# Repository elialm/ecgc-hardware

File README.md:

# ecgc-hardware

This repo contains all relevant documentation of the cartridge hardware.

The `legacy` directory contains legacy documentation.
This is just a collection of documents I made *waaaay* back when I was
just starting on the project.
It is included here just as an archive so I don't plan on updating anything.

The `CartGen3ProtoBoard` directory contains the schematics for the
first working prototype mentioned at [my website](https://efacdev.nl/posts/ecgc/20220601).
The photograph below is this prototype.

[gen3prototype-photo](https://user-images.githubusercontent.com/43206514/217519505-81669f43-df62-44b2-97f7-6338e39c4504.png)

The `CartGen4` directory contains the schematics for the
next prototype.
I've included some renders of it below.

[gen4-render-front](/CartGen4/img/front.png)  
[gen4-render-back](/CartGen4/img/back.png)

# Development tools

The tools used to make the schematics is [KiCad](https://www.kicad.org/).
It can be used to open the `*.kicad_pro` file to open the schematic
project.

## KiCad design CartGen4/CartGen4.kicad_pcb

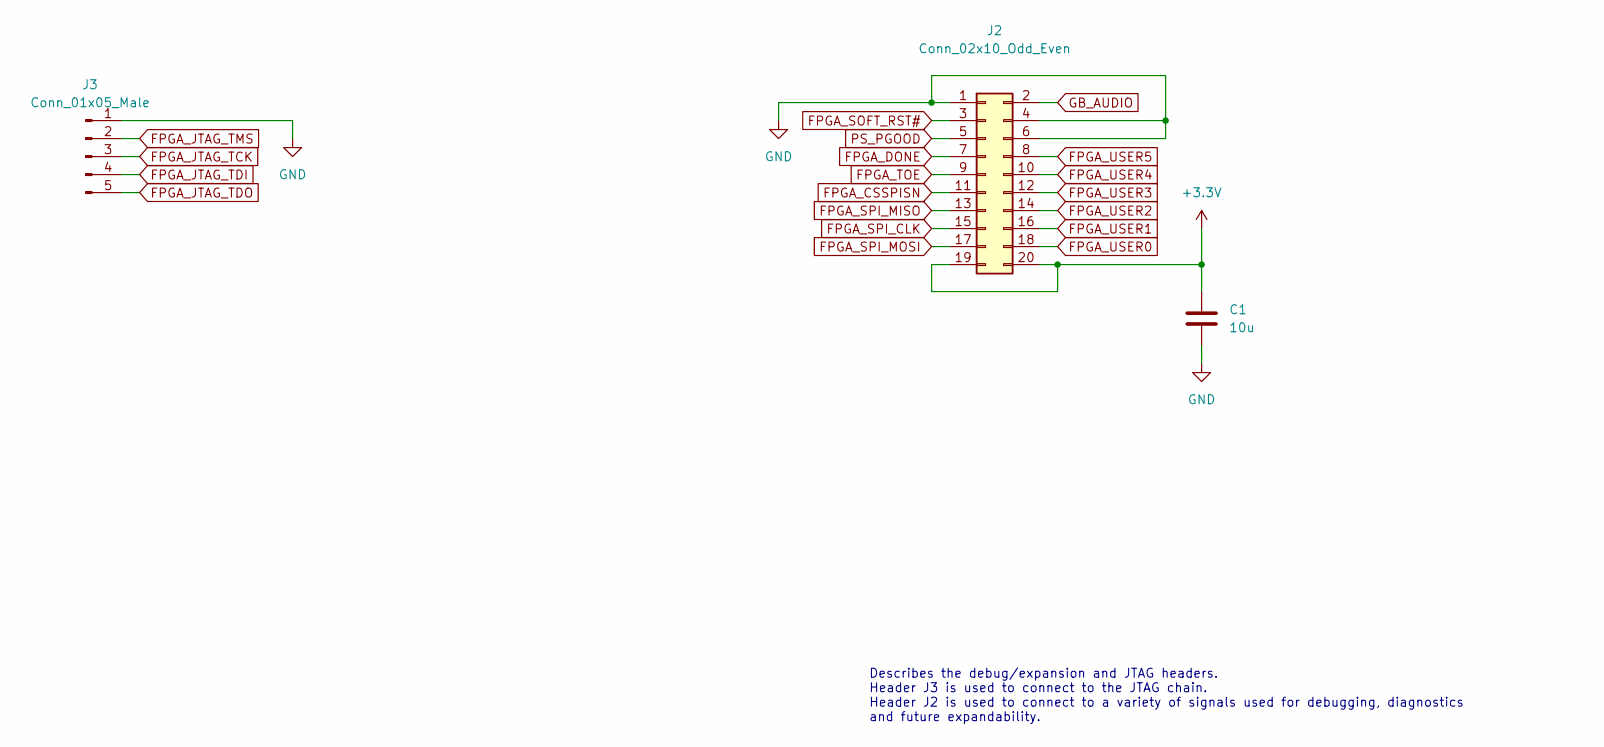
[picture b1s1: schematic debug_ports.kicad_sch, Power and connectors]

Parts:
C1: 10u; C_0603_1608Metric_Pad1.08x0.95mm_HandSolder; Tolerance 20%; Voltage 10V
J2: Conn_02x10_Odd_Even; Conn_02x10
J3: Conn_01x05_Male; PinHeader_1x05_P1.27mm_Vertical

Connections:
FPGA_CSSPISN: J2.11; also elsewhere on the board
FPGA_DONE: J2.7; also elsewhere on the board
FPGA_JTAG_TCK: J3.3; also elsewhere on the board
FPGA_JTAG_TDI: J3.4; also elsewhere on the board
FPGA_JTAG_TDO: J3.5; also elsewhere on the board
FPGA_JTAG_TMS: J3.2; also elsewhere on the board
FPGA_SOFT_RST#: J2.3; also elsewhere on the board
FPGA_SPI_CLK: J2.15; also elsewhere on the board
FPGA_SPI_MISO: J2.13; also elsewhere on the board
FPGA_SPI_MOSI: J2.17; also elsewhere on the board
FPGA_TOE: J2.9; also elsewhere on the board
FPGA_USER0: J2.18; also elsewhere on the board
FPGA_USER1: J2.16; also elsewhere on the board
FPGA_USER2: J2.14; also elsewhere on the board
FPGA_USER3: J2.12; also elsewhere on the board
FPGA_USER4: J2.10; also elsewhere on the board
FPGA_USER5: J2.8; also elsewhere on the board
GB_AUDIO: J2.2; also elsewhere on the board
GND: C1.2, J2.1, J2.4, J2.6, J3.1; also elsewhere on the board
PS_PGOOD: J2.5; also elsewhere on the board

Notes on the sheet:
Describes the debug/expansion and JTAG headers. Header J3 is used to connect to the JTAG chain. Header J2 is used to connect to a variety of signals used for debugging, diagnostics and future expandability.

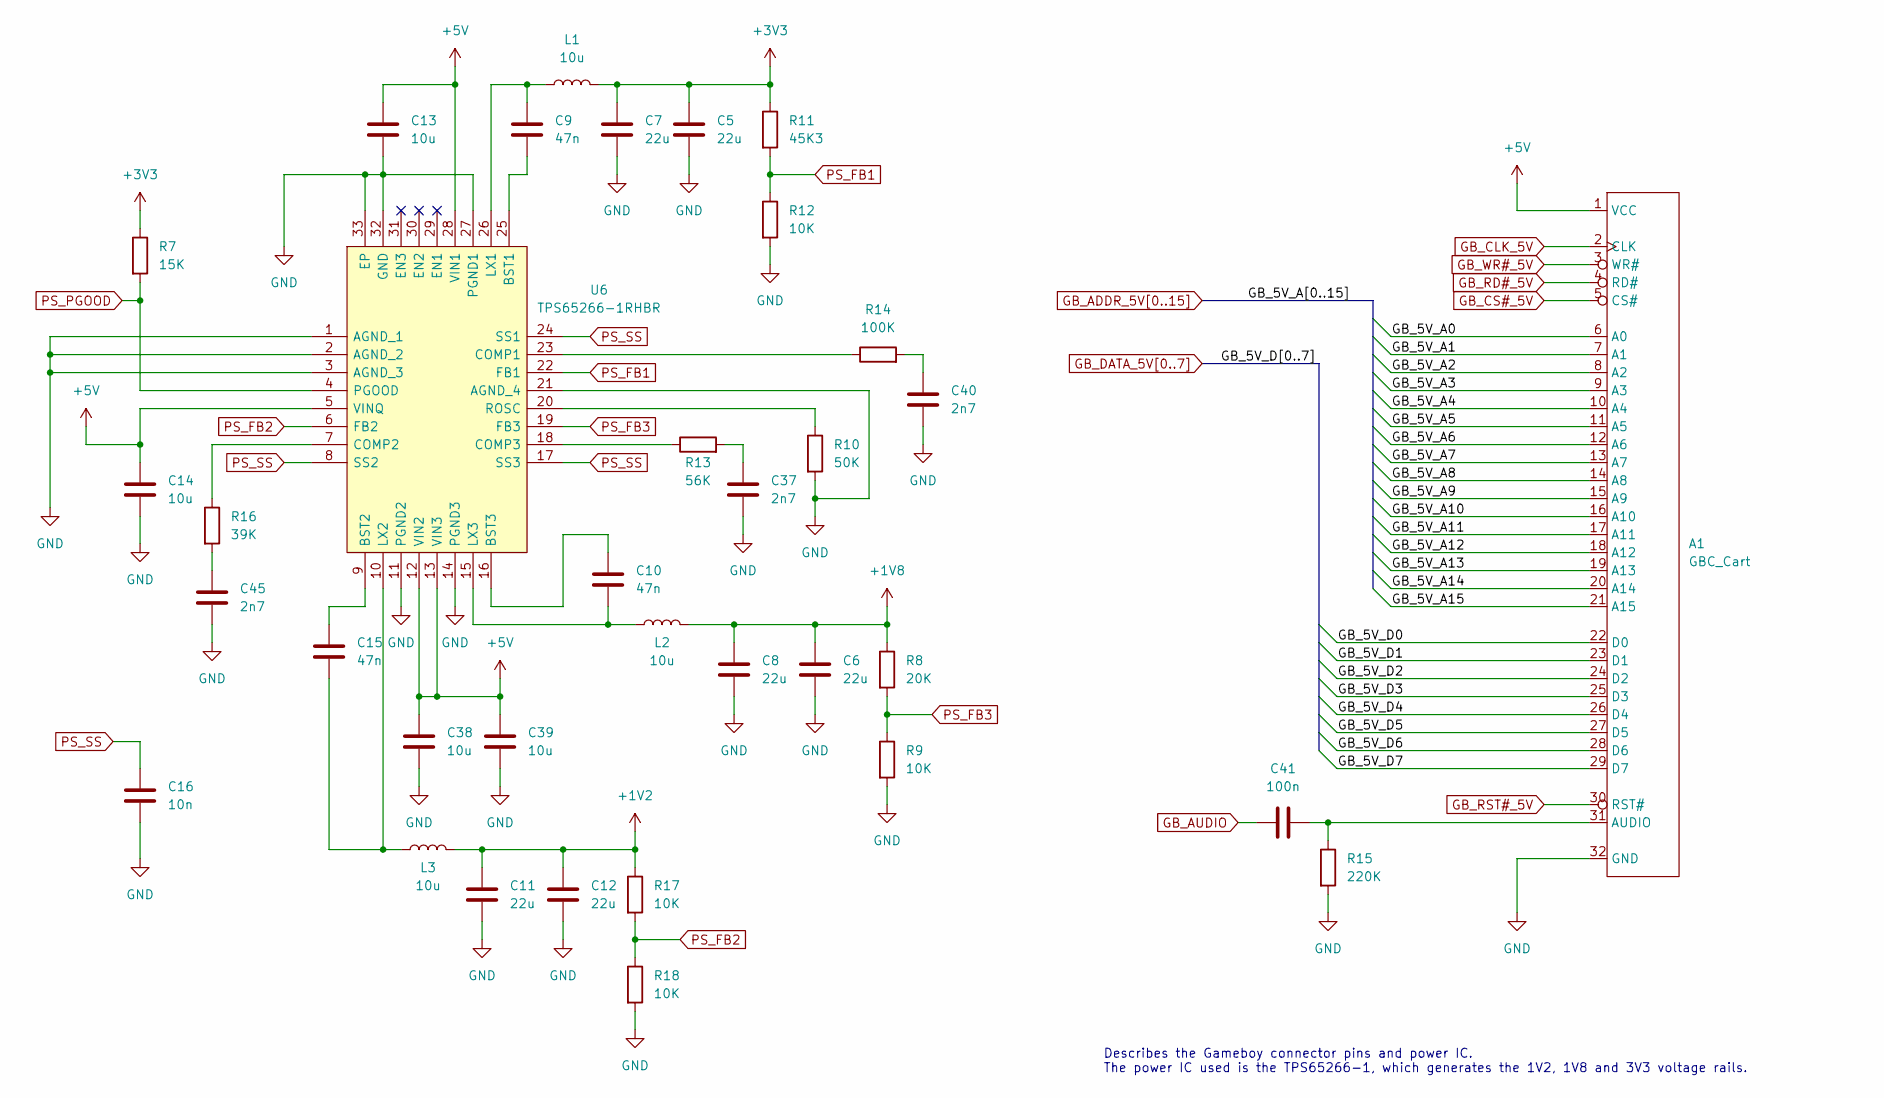
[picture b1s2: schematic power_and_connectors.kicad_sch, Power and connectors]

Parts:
A1: GBC_Cart
C5, C6, C7, C8, C11, C12: 22u; C_0603_1608Metric_Pad1.08x0.95mm_HandSolder; Tolerance 20%; Voltage 3V3
C9, C10, C15: 47n; C_0402_1005Metric_Pad0.74x0.62mm_HandSolder; Voltage 10V; Tolerance 5%
C13, C14, C38, C39: 10u; C_0603_1608Metric_Pad1.08x0.95mm_HandSolder; Voltage 10V; Tolerance 20%
C16: 10n; C_0402_1005Metric_Pad0.74x0.62mm_HandSolder; Tolerance 20%; Voltage 3V3
C37, C40, C45: 2n7; C_0402_1005Metric_Pad0.74x0.62mm_HandSolder; Tolerance 5%; Voltage 3V3
C41: 100n; C_0603_1608Metric_Pad1.08x0.95mm_HandSolder
L1, L2, L3: 10u; L_1008_2520Metric; Tolerance 20%
R7: 15K; R_0402_1005Metric_Pad0.72x0.64mm_HandSolder; Tolerance 10%
R8: 20K; R_0402_1005Metric_Pad0.72x0.64mm_HandSolder; Tolerance 1%
R9, R12, R17, R18: 10K; R_0402_1005Metric_Pad0.72x0.64mm_HandSolder; Tolerance 1%
R10: 50K; R_0402_1005Metric_Pad0.72x0.64mm_HandSolder; Tolerance 1%
R11: 45K3; R_0402_1005Metric_Pad0.72x0.64mm_HandSolder; Tolerance 1%
R13: 56K; R_0402_1005Metric_Pad0.72x0.64mm_HandSolder; Tolerance 1%
R14: 100K; R_0402_1005Metric_Pad0.72x0.64mm_HandSolder; Tolerance 1%
R15: 220K; R_0402_1005Metric_Pad0.72x0.64mm_HandSolder; Tolerance 10%
R16: 39K; R_0402_1005Metric_Pad0.72x0.64mm_HandSolder; Tolerance 1%
U6: TPS65266-1RHBR; QFN50P500X500X100-33N-D

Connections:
+1V2: C11.1, C12.1, L3.2, R17.1; also elsewhere on the board
+1V8: C6.1, C8.1, L2.2, R8.1; also elsewhere on the board
+5V: A1.1 (VCC), C13.1, C14.1, C38.1, C39.1, U6.5 (VINQ), U6.12 (VIN2), U6.13 (VIN3), U6.28 (VIN1); also elsewhere on the board
GB_ADDR_5V0: A1.6 (A0); also elsewhere on the board
GB_ADDR_5V1: A1.7 (A1); also elsewhere on the board
GB_ADDR_5V2: A1.8 (A2); also elsewhere on the board
GB_ADDR_5V3: A1.9 (A3); also elsewhere on the board
GB_ADDR_5V4: A1.10 (A4); also elsewhere on the board
GB_ADDR_5V5: A1.11 (A5); also elsewhere on the board
GB_ADDR_5V6: A1.12 (A6); also elsewhere on the board
GB_ADDR_5V7: A1.13 (A7); also elsewhere on the board
GB_ADDR_5V8: A1.14 (A8); also elsewhere on the board
GB_ADDR_5V9: A1.15 (A9); also elsewhere on the board
GB_ADDR_5V10: A1.16 (A10); also elsewhere on the board
GB_ADDR_5V11: A1.17 (A11); also elsewhere on the board
GB_ADDR_5V12: A1.18 (A12); also elsewhere on the board
GB_ADDR_5V13: A1.19 (A13); also elsewhere on the board
GB_ADDR_5V14: A1.20 (A14); also elsewhere on the board
GB_ADDR_5V15: A1.21 (A15); also elsewhere on the board
GB_AUDIO: C41.1; also elsewhere on the board
GB_CLK_5V: A1.2 (CLK); also elsewhere on the board
GB_CS#_5V: A1.5 (CS#); also elsewhere on the board
GB_DATA_5V0: A1.22 (D0); also elsewhere on the board
GB_DATA_5V1: A1.23 (D1); also elsewhere on the board
GB_DATA_5V2: A1.24 (D2); also elsewhere on the board
GB_DATA_5V3: A1.25 (D3); also elsewhere on the board
GB_DATA_5V4: A1.26 (D4); also elsewhere on the board
GB_DATA_5V5: A1.27 (D5); also elsewhere on the board
GB_DATA_5V6: A1.28 (D6); also elsewhere on the board
GB_DATA_5V7: A1.29 (D7); also elsewhere on the board
GB_RD#_5V: A1.4 (RD#); also elsewhere on the board
GB_RST#_5V: A1.30 (RST#); also elsewhere on the board
GB_WR#_5V: A1.3 (WR#); also elsewhere on the board
GND: A1.32 (GND), C5.2, C6.2, C7.2, C8.2, C11.2, C12.2, C13.2, C14.2, C16.2, C37.2, C38.2, C39.2, C40.2, C45.2, R9.2, R10.2, R12.2, R15.2, R18.2, U6.1 (AGND_1), U6.2 (AGND_2), U6.3 (AGND_3), U6.11 (PGND2), U6.14 (PGND3), U6.21 (AGND_4), U6.27 (PGND1), U6.32 (GND), U6.33 (EP); also elsewhere on the board
unnamed: A1.31 (AUDIO), C41.2, R15.1
unnamed: C45.1, R16.2
unnamed: C15.1, U6.9 (BST2)
unnamed: C15.2, L3.1, U6.10 (LX2)
unnamed: C9.1, L1.1, U6.26 (LX1)
unnamed: C9.2, U6.25 (BST1)
unnamed: C10.1, U6.16 (BST3)
unnamed: C10.2, L2.1, U6.15 (LX3)
unnamed: C37.1, R13.2
unnamed: C40.1, R14.2
unnamed: R16.1, U6.7 (COMP2)
unnamed: R13.1, U6.18 (COMP3)
unnamed: R10.1, U6.20 (ROSC)
unnamed: R14.1, U6.23 (COMP1)
PS_FB1: R11.2, R12.1, U6.22 (FB1)
PS_FB2: R17.2, R18.1, U6.6 (FB2)
PS_FB3: R8.2, R9.1, U6.19 (FB3)
PS_PGOOD: R7.2, U6.4 (PGOOD); also elsewhere on the board
PS_SS: C16.1, U6.8 (SS2), U6.17 (SS3), U6.24 (SS1)

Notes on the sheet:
Describes the Gameboy connector pins and power IC. The power IC used is the TPS65266-1, which generates the 1V2, 1V8 and 3V3 voltage rails.

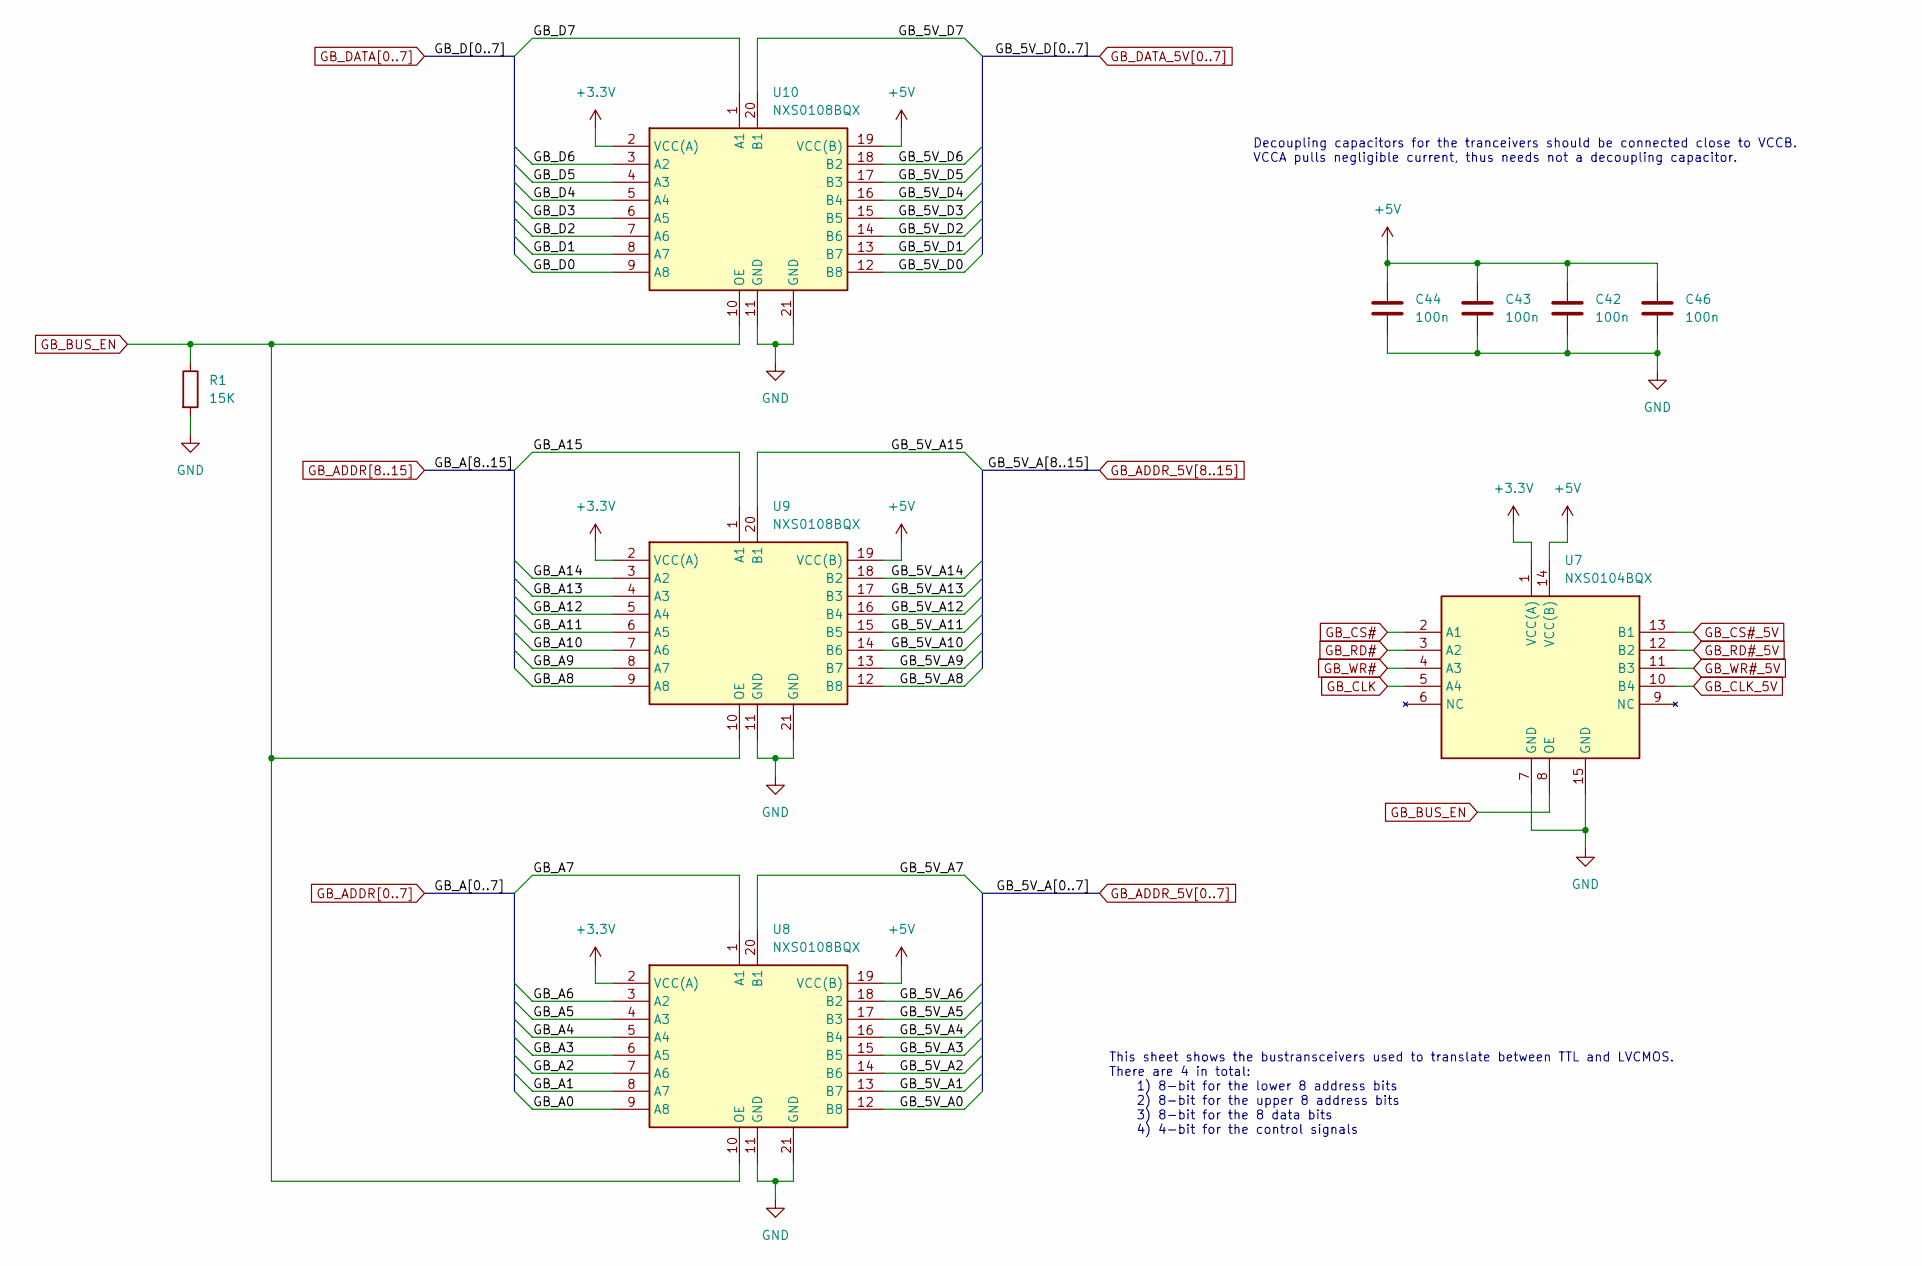
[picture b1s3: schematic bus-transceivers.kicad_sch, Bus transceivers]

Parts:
C42, C43, C44, C46: 100n; C_0402_1005Metric_Pad0.74x0.62mm_HandSolder; Tolerance 20%; Voltage 3V3
R1: 15K; R_0402_1005Metric_Pad0.72x0.64mm_HandSolder; Tolerance 10%
U7: NXS0104BQX
U8, U9, U10: NXS0108BQX

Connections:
+5V: C42.1, C43.1, C44.1, C46.1, U7.14 (VCC(B)), U8.19 (VCC(B)), U9.19 (VCC(B)), U10.19 (VCC(B)); also elsewhere on the board
GB_ADDR0: U8.9 (A8); also elsewhere on the board
GB_ADDR1: U8.8 (A7); also elsewhere on the board
GB_ADDR2: U8.7 (A6); also elsewhere on the board
GB_ADDR3: U8.6 (A5); also elsewhere on the board
GB_ADDR4: U8.5 (A4); also elsewhere on the board
GB_ADDR5: U8.4 (A3); also elsewhere on the board
GB_ADDR6: U8.3 (A2); also elsewhere on the board
GB_ADDR7: U8.1 (A1); also elsewhere on the board
GB_ADDR8: U9.9 (A8); also elsewhere on the board
GB_ADDR9: U9.8 (A7); also elsewhere on the board
GB_ADDR10: U9.7 (A6); also elsewhere on the board
GB_ADDR11: U9.6 (A5); also elsewhere on the board
GB_ADDR12: U9.5 (A4); also elsewhere on the board
GB_ADDR13: U9.4 (A3); also elsewhere on the board
GB_ADDR14: U9.3 (A2); also elsewhere on the board
GB_ADDR15: U9.1 (A1); also elsewhere on the board
GB_ADDR_5V0: U8.12 (B8); also elsewhere on the board
GB_ADDR_5V1: U8.13 (B7); also elsewhere on the board
GB_ADDR_5V2: U8.14 (B6); also elsewhere on the board
GB_ADDR_5V3: U8.15 (B5); also elsewhere on the board
GB_ADDR_5V4: U8.16 (B4); also elsewhere on the board
GB_ADDR_5V5: U8.17 (B3); also elsewhere on the board
GB_ADDR_5V6: U8.18 (B2); also elsewhere on the board
GB_ADDR_5V7: U8.20 (B1); also elsewhere on the board
GB_ADDR_5V8: U9.12 (B8); also elsewhere on the board
GB_ADDR_5V9: U9.13 (B7); also elsewhere on the board
GB_ADDR_5V10: U9.14 (B6); also elsewhere on the board
GB_ADDR_5V11: U9.15 (B5); also elsewhere on the board
GB_ADDR_5V12: U9.16 (B4); also elsewhere on the board
GB_ADDR_5V13: U9.17 (B3); also elsewhere on the board
GB_ADDR_5V14: U9.18 (B2); also elsewhere on the board
GB_ADDR_5V15: U9.20 (B1); also elsewhere on the board
GB_BUS_EN: R1.1, U7.8 (OE), U8.10 (OE), U9.10 (OE), U10.10 (OE); also elsewhere on the board
GB_CLK: U7.5 (A4); also elsewhere on the board
GB_CLK_5V: U7.10 (B4); also elsewhere on the board
GB_CS#: U7.2 (A1); also elsewhere on the board
GB_CS#_5V: U7.13 (B1); also elsewhere on the board
GB_DATA0: U10.9 (A8); also elsewhere on the board
GB_DATA1: U10.8 (A7); also elsewhere on the board
GB_DATA2: U10.7 (A6); also elsewhere on the board
GB_DATA3: U10.6 (A5); also elsewhere on the board
GB_DATA4: U10.5 (A4); also elsewhere on the board
GB_DATA5: U10.4 (A3); also elsewhere on the board
GB_DATA6: U10.3 (A2); also elsewhere on the board
GB_DATA7: U10.1 (A1); also elsewhere on the board
GB_DATA_5V0: U10.12 (B8); also elsewhere on the board
GB_DATA_5V1: U10.13 (B7); also elsewhere on the board
GB_DATA_5V2: U10.14 (B6); also elsewhere on the board
GB_DATA_5V3: U10.15 (B5); also elsewhere on the board
GB_DATA_5V4: U10.16 (B4); also elsewhere on the board
GB_DATA_5V5: U10.17 (B3); also elsewhere on the board
GB_DATA_5V6: U10.18 (B2); also elsewhere on the board
GB_DATA_5V7: U10.20 (B1); also elsewhere on the board
GB_RD#: U7.3 (A2); also elsewhere on the board
GB_RD#_5V: U7.12 (B2); also elsewhere on the board
GB_WR#: U7.4 (A3); also elsewhere on the board
GB_WR#_5V: U7.11 (B3); also elsewhere on the board
GND: C42.2, C43.2, C44.2, C46.2, R1.2, U7.7 (GND), U7.15 (GND), U8.11 (GND), U8.21 (GND), U9.11 (GND), U9.21 (GND), U10.11 (GND), U10.21 (GND); also elsewhere on the board

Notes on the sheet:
This sheet shows the bustransceivers used to translate between TTL and LVCMOS. There are 4 in total: 1) 8-bit for the lower 8 address bits 2) 8-bit for the upper 8 address bits 3) 8-bit for the 8 data bits 4) 4-bit for the control signals
Decoupling capacitors for the tranceivers should be connected close to VCCB. VCCA pulls negligible current, thus needs not a decoupling capacitor.

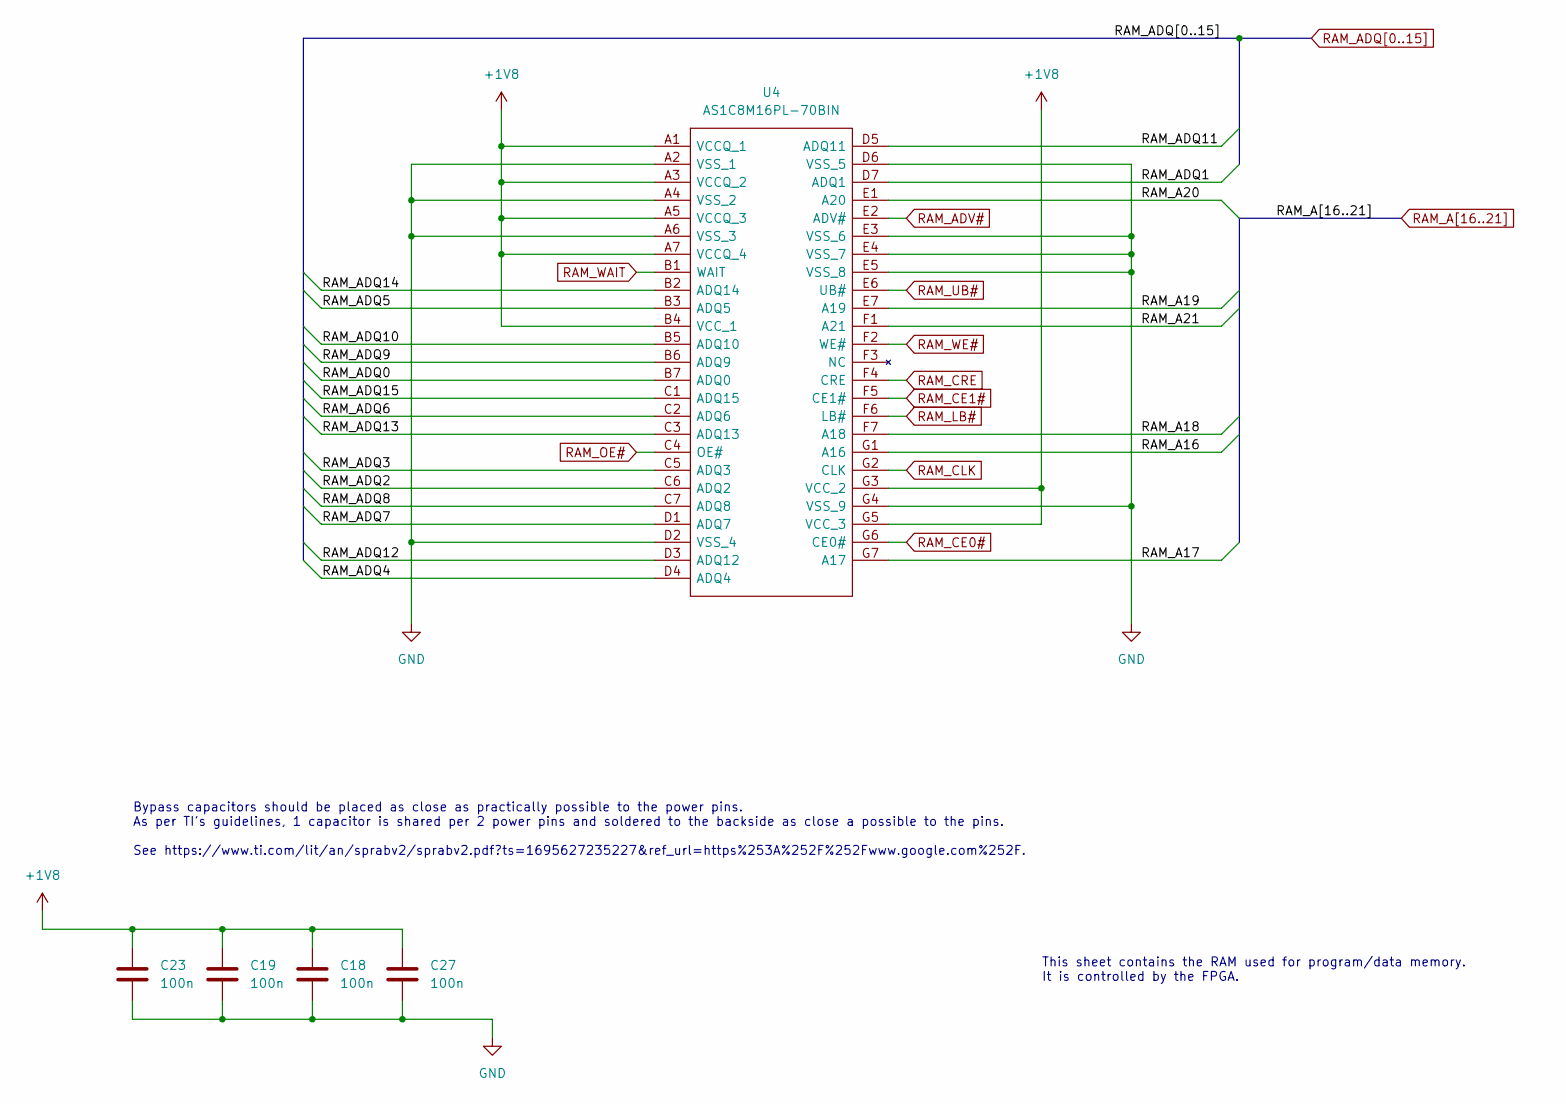
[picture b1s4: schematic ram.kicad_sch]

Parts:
C18, C19, C23, C27: 100n; C_0402_1005Metric_Pad0.74x0.62mm_HandSolder; Tolerance 20%; Voltage 3V3
U4: AS1C8M16PL-70BIN; BGA49C50P7X7_400X400X100

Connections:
+1V8: C18.1, C19.1, C23.1, C27.1, U4.A1 (VCCQ_1), U4.A3 (VCCQ_2), U4.A5 (VCCQ_3), U4.A7 (VCCQ_4), U4.B4 (VCC_1), U4.G3 (VCC_2), U4.G5 (VCC_3); also elsewhere on the board
GND: C18.2, C19.2, C23.2, C27.2, U4.A2 (VSS_1), U4.A4 (VSS_2), U4.A6 (VSS_3), U4.D2 (VSS_4), U4.D6 (VSS_5), U4.E3 (VSS_6), U4.E4 (VSS_7), U4.E5 (VSS_8), U4.G4 (VSS_9); also elsewhere on the board
RAM_A16: U4.G1 (A16); also elsewhere on the board
RAM_A17: U4.G7 (A17); also elsewhere on the board
RAM_A18: U4.F7 (A18); also elsewhere on the board
RAM_A19: U4.E7 (A19); also elsewhere on the board
RAM_A20: U4.E1 (A20); also elsewhere on the board
RAM_A21: U4.F1 (A21); also elsewhere on the board
RAM_ADQ0: U4.B7 (ADQ0); also elsewhere on the board
RAM_ADQ1: U4.D7 (ADQ1); also elsewhere on the board
RAM_ADQ2: U4.C6 (ADQ2); also elsewhere on the board
RAM_ADQ3: U4.C5 (ADQ3); also elsewhere on the board
RAM_ADQ4: U4.D4 (ADQ4); also elsewhere on the board
RAM_ADQ5: U4.B3 (ADQ5); also elsewhere on the board
RAM_ADQ6: U4.C2 (ADQ6); also elsewhere on the board
RAM_ADQ7: U4.D1 (ADQ7); also elsewhere on the board
RAM_ADQ8: U4.C7 (ADQ8); also elsewhere on the board
RAM_ADQ9: U4.B6 (ADQ9); also elsewhere on the board
RAM_ADQ10: U4.B5 (ADQ10); also elsewhere on the board
RAM_ADQ11: U4.D5 (ADQ11); also elsewhere on the board
RAM_ADQ12: U4.D3 (ADQ12); also elsewhere on the board
RAM_ADQ13: U4.C3 (ADQ13); also elsewhere on the board
RAM_ADQ14: U4.B2 (ADQ14); also elsewhere on the board
RAM_ADQ15: U4.C1 (ADQ15); also elsewhere on the board
RAM_ADV#: U4.E2 (ADV#); also elsewhere on the board
RAM_CE0#: U4.G6 (CE0#); also elsewhere on the board
RAM_CE1#: U4.F5 (CE1#); also elsewhere on the board
RAM_CLK: U4.G2 (CLK); also elsewhere on the board
RAM_CRE: U4.F4 (CRE); also elsewhere on the board
RAM_LB#: U4.F6 (LB#); also elsewhere on the board
RAM_OE#: U4.C4 (OE#); also elsewhere on the board
RAM_UB#: U4.E6 (UB#); also elsewhere on the board
RAM_WAIT: U4.B1 (WAIT); also elsewhere on the board
RAM_WE#: U4.F2 (WE#); also elsewhere on the board

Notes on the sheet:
This sheet contains the RAM used for program/data memory. It is controlled by the FPGA.
Bypass capacitors should be placed as close as practically possible to the power pins. As per TI's guidelines, 1 capacitor is shared per 2 power pins and soldered to the backside as close a possible to the pins. See https://www.ti.com/lit/an/sprabv2/sprabv2.pdf?ts=1695627235227&ref_url=https%253A%2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

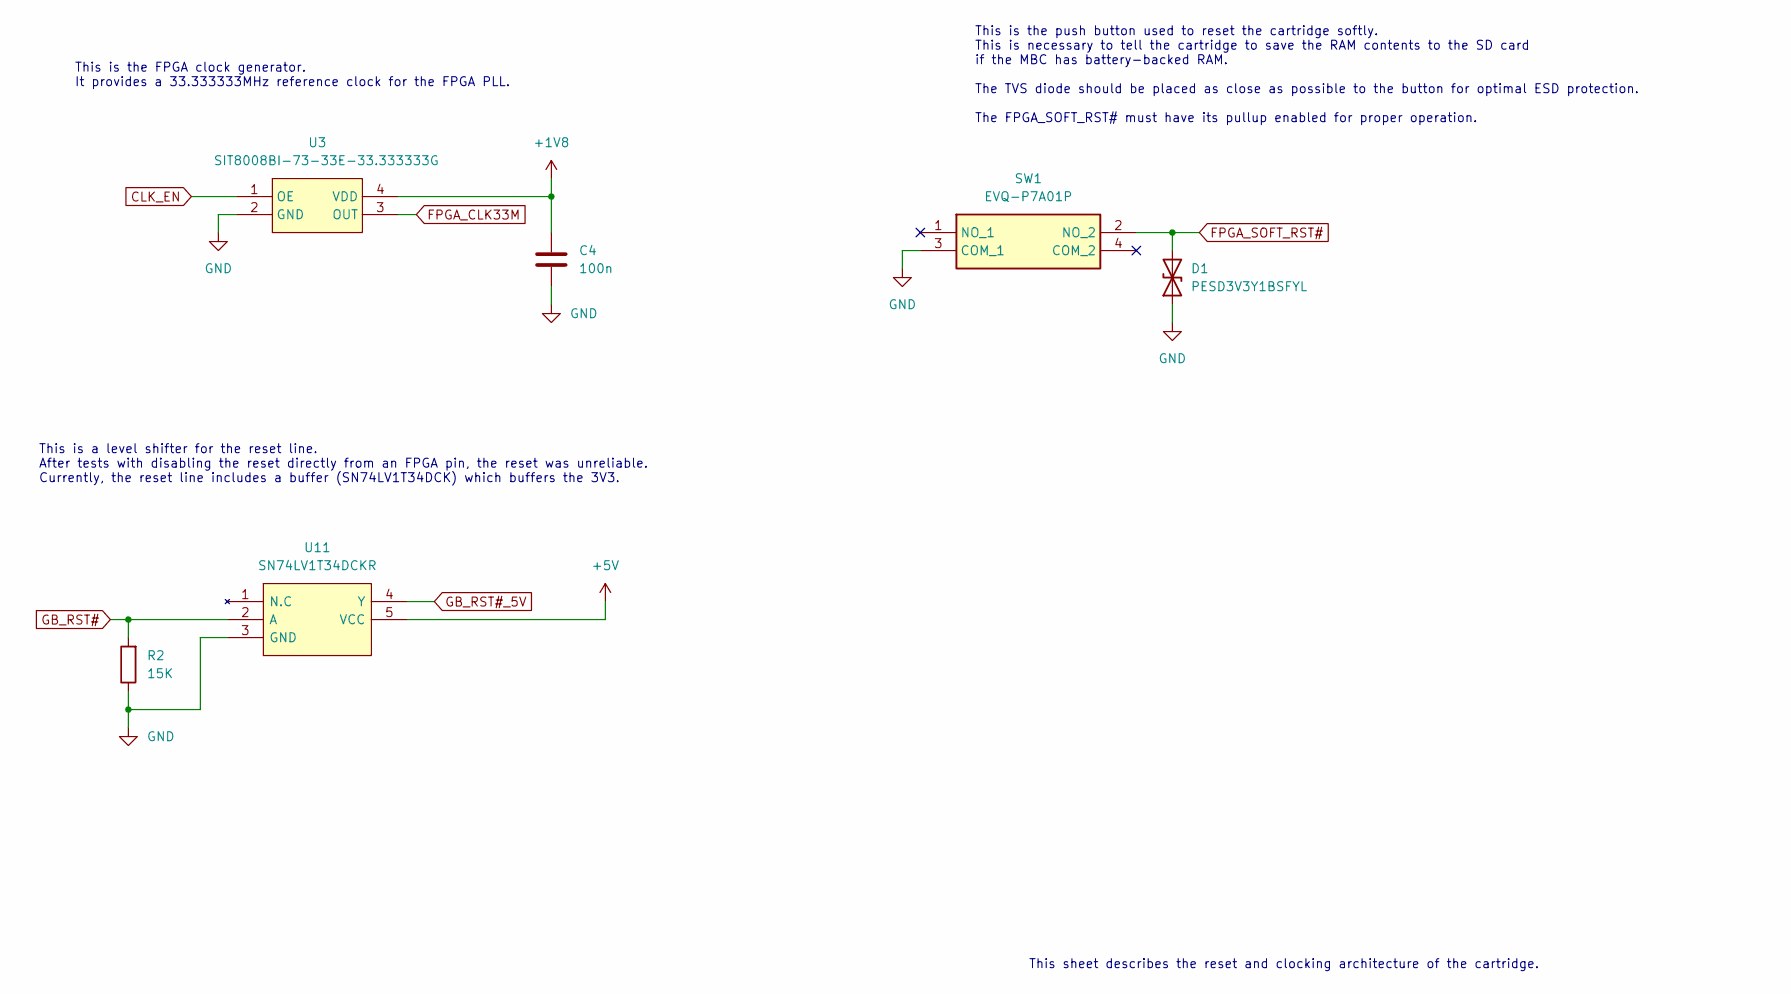
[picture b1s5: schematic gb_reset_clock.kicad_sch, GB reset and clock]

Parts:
C4: 100n; C_0402_1005Metric_Pad0.74x0.62mm_HandSolder; Tolerance 20%; Voltage 3V3
D1: PESD3V3Y1BSFYL; Voltage 3V3
R2: 15K; R_0402_1005Metric_Pad0.72x0.64mm_HandSolder; Tolerance 10%
SW1: EVQ-P7A01P; EVQP7J01P
U3: SIT8008BI-73-33E-33.333333G
U11: SN74LV1T34DCKR; SOT65P210X110-5N

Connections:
+1V8: C4.1, U3.4 (VDD); also elsewhere on the board
+5V: U11.5 (VCC); also elsewhere on the board
CLK_EN: U3.1 (OE); also elsewhere on the board
FPGA_CLK33M: U3.3 (OUT); also elsewhere on the board
FPGA_SOFT_RST#: D1.2 (A2), SW1.2 (NO_2); also elsewhere on the board
GB_RST#: R2.2, U11.2 (A); also elsewhere on the board
GB_RST#_5V: U11.4 (Y); also elsewhere on the board
GND: C4.2, D1.1 (A1), R2.1, SW1.3 (COM_1), U3.2 (GND), U11.3 (GND); also elsewhere on the board

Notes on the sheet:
This is the push button used to reset the cartridge softly. This is necessary to tell the cartridge to save the RAM contents to the SD card if the MBC has battery-backed RAM. The TVS diode should be placed as close as possible to the button for optimal ESD protection. The FPGA_SOFT_RST# must have i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
This is a level shifter for the reset line. After tests with disabling the reset directly from an FPGA pin, the reset was unreliable. Currently, the reset line includes a buffer (SN74LV1T34DCK) which buffers the 3V3.
This sheet describes the reset and clocking architecture of the cartridge.
This is the FPGA clock generator. It provides a 33.333333MHz reference clock for the FPGA PLL.

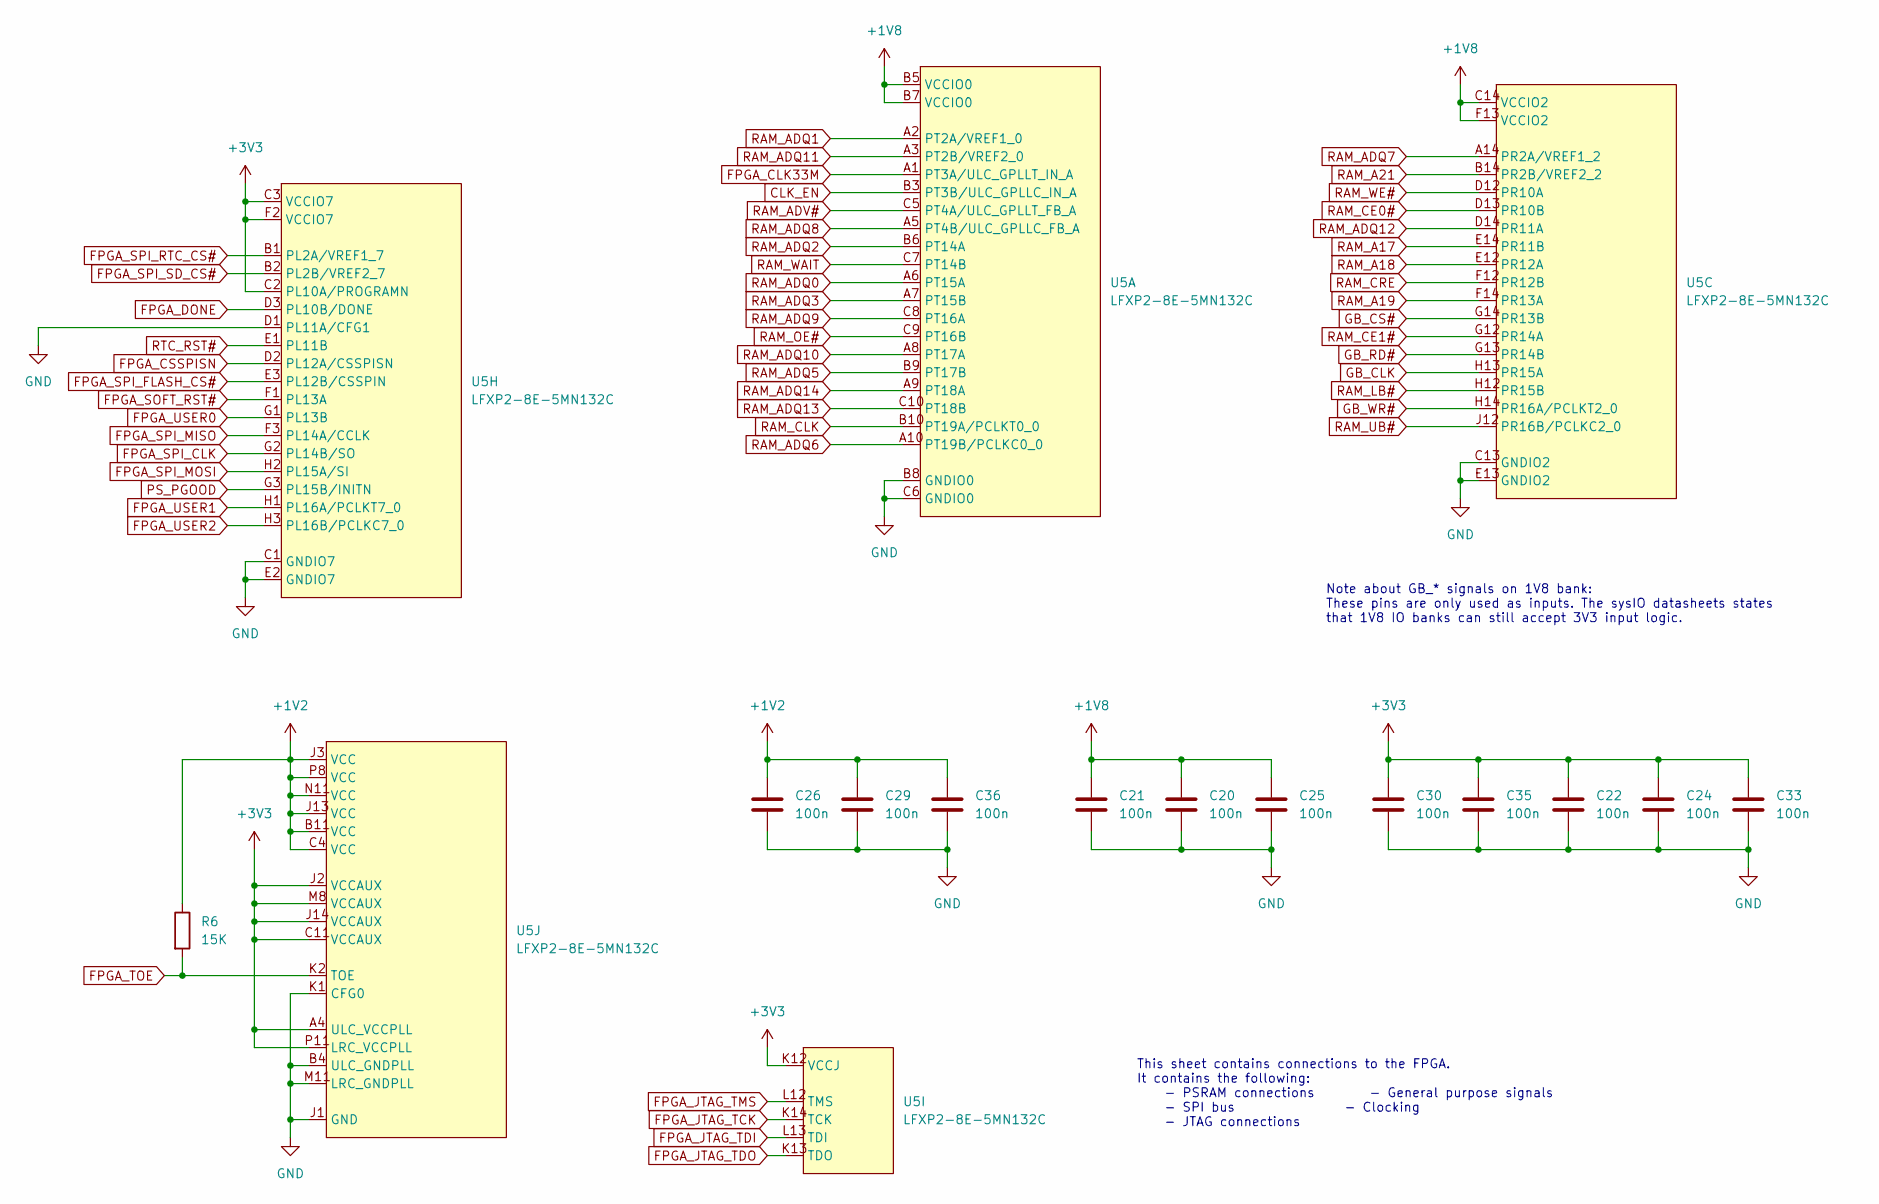
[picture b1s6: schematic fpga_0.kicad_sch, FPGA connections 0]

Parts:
C20, C21, C22, C24, C25, C26, C29, C30, C33, C35, C36: 100n; C_0402_1005Metric_Pad0.74x0.62mm_HandSolder; Tolerance 20%; Voltage 3V3
R6: 15K; R_0402_1005Metric_Pad0.72x0.64mm_HandSolder; Tolerance 10%
U5: LFXP2-8E-5MN132C; BGA132C50P14X14_800X800X135

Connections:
+1V2: C26.1, C29.1, C36.1, R6.1, U5.B11 (VCC), U5.C4 (VCC), U5.J3 (VCC), U5.J13 (VCC), U5.N11 (VCC), U5.P8 (VCC); also elsewhere on the board
+1V8: C20.1, C21.1, C25.1, U5.B5 (VCCIO0), U5.B7 (VCCIO0), U5.C14 (VCCIO2), U5.F13 (VCCIO2); also elsewhere on the board
CLK_EN: U5.B3 (PT3B/ULC_GPLLC_IN_A); also elsewhere on the board
FPGA_CLK33M: U5.A1 (PT3A/ULC_GPLLT_IN_A); also elsewhere on the board
FPGA_CSSPISN: U5.D2 (PL12A/CSSPISN); also elsewhere on the board
FPGA_DONE: U5.D3 (PL10B/DONE); also elsewhere on the board
FPGA_JTAG_TCK: U5.K14 (TCK); also elsewhere on the board
FPGA_JTAG_TDI: U5.L13 (TDI); also elsewhere on the board
FPGA_JTAG_TDO: U5.K13 (TDO); also elsewhere on the board
FPGA_JTAG_TMS: U5.L12 (TMS); also elsewhere on the board
FPGA_SOFT_RST#: U5.F1 (PL13A); also elsewhere on the board
FPGA_SPI_CLK: U5.G2 (PL14B/SO); also elsewhere on the board
FPGA_SPI_FLASH_CS#: U5.E3 (PL12B/CSSPIN); also elsewhere on the board
FPGA_SPI_MISO: U5.F3 (PL14A/CCLK); also elsewhere on the board
FPGA_SPI_MOSI: U5.H2 (PL15A/SI); also elsewhere on the board
FPGA_SPI_RTC_CS#: U5.B1 (PL2A/VREF1_7); also elsewhere on the board
FPGA_SPI_SD_CS#: U5.B2 (PL2B/VREF2_7); also elsewhere on the board
FPGA_TOE: R6.2, U5.K2 (TOE); also elsewhere on the board
FPGA_USER0: U5.G1 (PL13B); also elsewhere on the board
FPGA_USER1: U5.H1 (PL16A/PCLKT7_0); also elsewhere on the board
FPGA_USER2: U5.H3 (PL16B/PCLKC7_0); also elsewhere on the board
GB_CLK: U5.H13 (PR15A); also elsewhere on the board
GB_CS#: U5.G14 (PR13B); also elsewhere on the board
GB_RD#: U5.G13 (PR14B); also elsewhere on the board
GB_WR#: U5.H14 (PR16A/PCLKT2_0); also elsewhere on the board
GND: C20.2, C21.2, C22.2, C24.2, C25.2, C26.2, C29.2, C30.2, C33.2, C35.2, C36.2, U5.B4 (ULC_GNDPLL), U5.B8 (GNDIO0), U5.C1 (GNDIO7), U5.C6 (GNDIO0), U5.C13 (GNDIO2), U5.D1 (PL11A/CFG1), U5.E2 (GNDIO7), U5.E13 (GNDIO2), U5.J1 (GND), U5.K1 (CFG0), U5.M11 (LRC_GNDPLL); also elsewhere on the board
PS_PGOOD: U5.G3 (PL15B/INITN); also elsewhere on the board
RAM_A17: U5.E14 (PR11B); also elsewhere on the board
RAM_A18: U5.E12 (PR12A); also elsewhere on the board
RAM_A19: U5.F14 (PR13A); also elsewhere on the board
RAM_A21: U5.B14 (PR2B/VREF2_2); also elsewhere on the board
RAM_ADQ0: U5.A6 (PT15A); also elsewhere on the board
RAM_ADQ1: U5.A2 (PT2A/VREF1_0); also elsewhere on the board
RAM_ADQ2: U5.B6 (PT14A); also elsewhere on the board
RAM_ADQ3: U5.A7 (PT15B); also elsewhere on the board
RAM_ADQ5: U5.B9 (PT17B); also elsewhere on the board
RAM_ADQ6: U5.A10 (PT19B/PCLKC0_0); also elsewhere on the board
RAM_ADQ7: U5.A14 (PR2A/VREF1_2); also elsewhere on the board
RAM_ADQ8: U5.A5 (PT4B/ULC_GPLLC_FB_A); also elsewhere on the board
RAM_ADQ9: U5.C8 (PT16A); also elsewhere on the board
RAM_ADQ10: U5.A8 (PT17A); also elsewhere on the board
RAM_ADQ11: U5.A3 (PT2B/VREF2_0); also elsewhere on the board
RAM_ADQ12: U5.D14 (PR11A); also elsewhere on the board
RAM_ADQ13: U5.C10 (PT18B); also elsewhere on the board
RAM_ADQ14: U5.A9 (PT18A); also elsewhere on the board
RAM_ADV#: U5.C5 (PT4A/ULC_GPLLT_FB_A); also elsewhere on the board
RAM_CE0#: U5.D13 (PR10B); also elsewhere on the board
RAM_CE1#: U5.G12 (PR14A); also elsewhere on the board
RAM_CLK: U5.B10 (PT19A/PCLKT0_0); also elsewhere on the board
RAM_CRE: U5.F12 (PR12B); also elsewhere on the board
RAM_LB#: U5.H12 (PR15B); also elsewhere on the board
RAM_OE#: U5.C9 (PT16B); also elsewhere on the board
RAM_UB#: U5.J12 (PR16B/PCLKC2_0); also elsewhere on the board
RAM_WAIT: U5.C7 (PT14B); also elsewhere on the board
RAM_WE#: U5.D12 (PR10A); also elsewhere on the board
RTC_RST#: U5.E1 (PL11B); also elsewhere on the board

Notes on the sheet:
This sheet contains connections to the FPGA. It contains the following: - PSRAM connections - General purpose signals - SPI bus - Clocking - JTAG connections
Note about GB_* signals on 1V8 bank: These pins are only used as inputs. The sysIO datasheets states that 1V8 IO banks can still accept 3V3 input logic.

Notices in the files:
CartGen4/CartGen4.kicad_pcb:
© 2023 Elijah Almeida Coimbra
CartGen4/bus-transceivers.kicad_sch:
© Elijah Almeida Coimbra
